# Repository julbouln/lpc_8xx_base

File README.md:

[NXP's LPC800 family microcontroller](http://www.nxp.com/products/microcontrollers/cortex_m0_m0/lpc800/) development code base.

The code should work with LPC810, LPC811 and LPC812.

The code is based on [LPCOpen 2](http://www.lpcware.com/content/nxpfile/lpcopen-software-development-platform-lpc8xx-packages) source code and [sebseb7/lpc8xx Makefile](https://github.com/sebseb7/lpc8xx) (arm-none-eabi toolchain). The main addition is C++ capability and an Arduino like compatible API.

Supported Arduino functions and libraries :

* pinMode, digitalWrite, digitalRead
* delay
* Serial
* SPI
* Wire

INO files can be compiled with ino2firmware.sh script.

Code come with an hardware implementation composed of a MCP2200 USB to UART and a LPC812 chip.
https://github.com/julbouln/mcp2200_simpleio and lpc21isp must be installed and tools in tools/ compiled to use "make flash" which upload firmware.hex.

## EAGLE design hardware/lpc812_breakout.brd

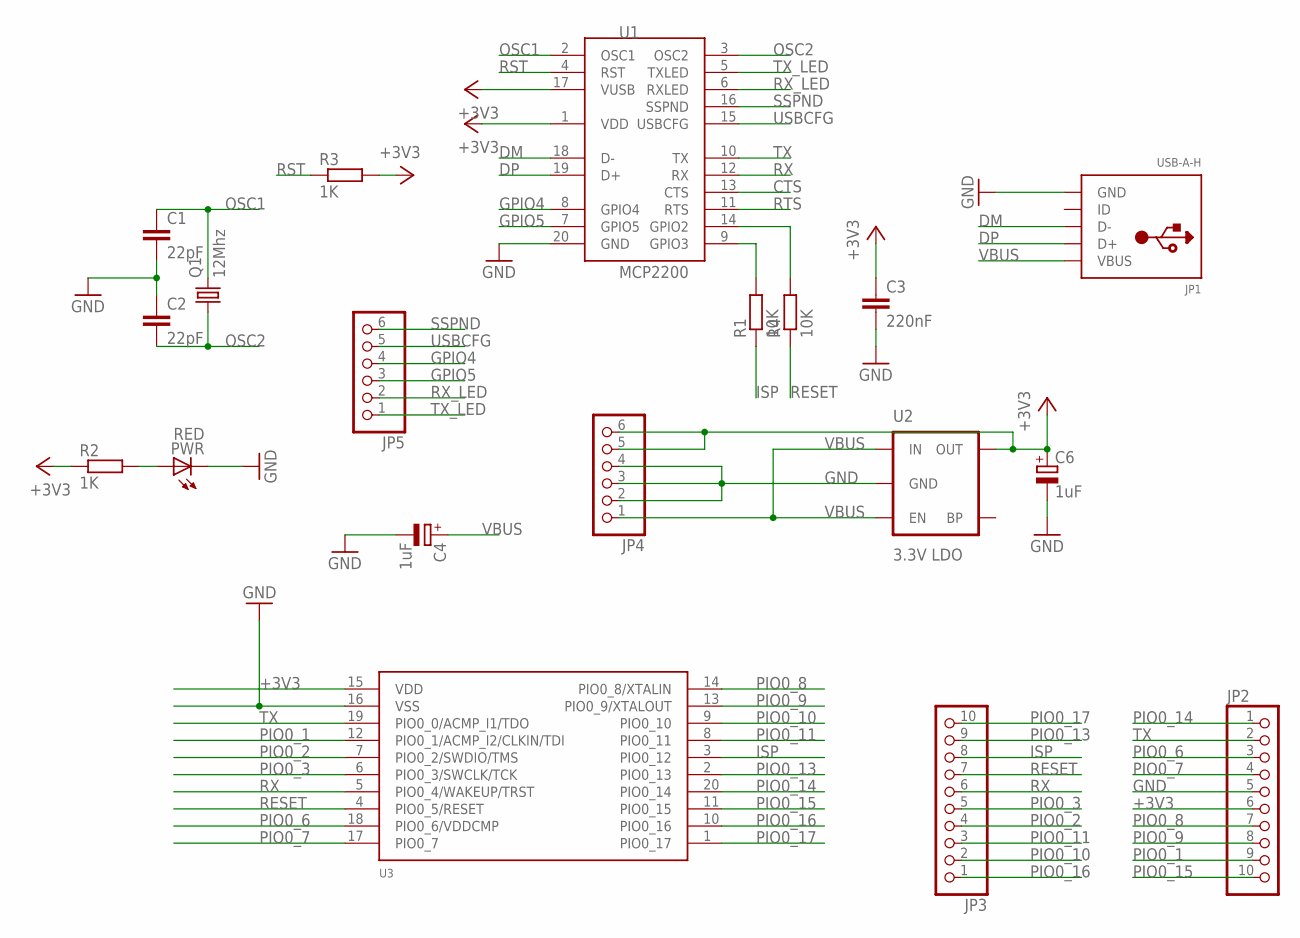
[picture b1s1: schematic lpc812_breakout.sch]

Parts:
C1, C2: 22pF; C1206
C3: 220nF; C1206
C4, C6: 1uF; A/3216-18R
JP1: USB-A-H; USB-MINIB-THM-MOLEX
JP2, JP3: HEADER-1X10ROUND; 1X10_ROUND
JP4, JP5: HEADER-1X6ROUND; 1X06_ROUND
PWR: RED; 1206
Q1: 12Mhz; HC49/S
R1, R4: 10K; R1206
R2, R3: 1K; R1206
U1: MCP2200; SSOP20
U2: 3.3V LDO; SOT23-5
U3: LPC812M101JDH20; TSSOP20

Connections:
+3V3: C3.1, C6.+, JP2.6, JP4.5, JP4.6, R2.1, R3.2, U1.1 (VDD), U1.17 (VUSB), U2.5 (OUT), U3.15 (VDD)
CTS: U1.13 (CTS)
DM: JP1.D-, U1.18 (D-)
DP: JP1.D+, U1.19 (D+)
GND: C1.2, C2.1, C3.2, C4.-, C6.-, JP1.GND, JP2.5, JP4.2, JP4.3, JP4.4, PWR.C, U1.20 (GND), U2.2 (GND), U3.16 (VSS)
GPIO4: JP5.4, U1.8 (GPIO4)
GPIO5: JP5.3, U1.7 (GPIO5)
ISP: JP3.8, R1.1, U3.3 (PIO0_12)
unnamed: PWR.A, R2.2
unnamed: R1.2, U1.9 (GPIO3)
unnamed: R4.2, U1.14 (GPIO2)
OSC1: C1.1, Q1.2, U1.2 (OSC1)
OSC2: C2.2, Q1.1, U1.3 (OSC2)
PIO0_1: JP2.9, U3.12 (PIO0_1/ACMP_I2/CLKIN/TDI)
PIO0_2: JP3.4, U3.7 (PIO0_2/SWDIO/TMS)
PIO0_3: JP3.5, U3.6 (PIO0_3/SWCLK/TCK)
PIO0_6: JP2.3, U3.18 (PIO0_6/VDDCMP)
PIO0_7: JP2.4, U3.17 (PIO0_7)
PIO0_8: JP2.7, U3.14 (PIO0_8/XTALIN)
PIO0_9: JP2.8, U3.13 (PIO0_9/XTALOUT)
PIO0_10: JP3.2, U3.9 (PIO0_10)
PIO0_11: JP3.3, U3.8 (PIO0_11)
PIO0_13: JP3.9, U3.2 (PIO0_13)
PIO0_14: JP2.1, U3.20 (PIO0_14)
PIO0_15: JP2.10, U3.11 (PIO0_15)
PIO0_16: JP3.1, U3.10 (PIO0_16)
PIO0_17: JP3.10, U3.1 (PIO0_17)
RESET: JP3.7, R4.1, U3.4 (PIO0_5/RESET)
RST: R3.1, U1.4 (RST)
RTS: U1.11 (RTS)
RX: JP3.6, U1.12 (RX), U3.5 (PIO0_4/WAKEUP/TRST)
RX_LED: JP5.2, U1.6 (RXLED)
SSPND: JP5.6, U1.16 (SSPND)
TX: JP2.2, U1.10 (TX), U3.19 (PIO0_0/ACMP_I1/TDO)
TX_LED: JP5.1, U1.5 (TXLED)
USBCFG: JP5.5, U1.15 (USBCFG)
VBUS: C4.+, JP1.VBUS, JP4.1, U2.1 (IN), U2.3 (EN)

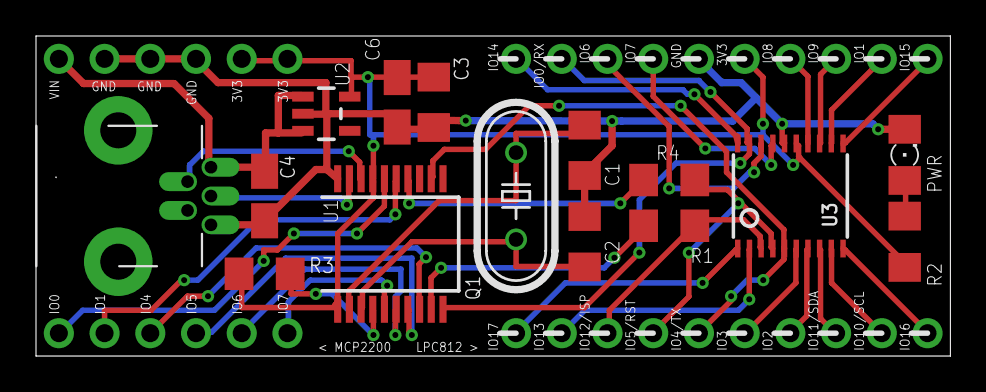
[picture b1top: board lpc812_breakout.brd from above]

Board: 2 copper layers, 50.8 x 17.8 mm, 20 parts (1 on the bottom side), 35 nets.

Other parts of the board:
U$1: PANDA

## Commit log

2014-06-14 cleanup
2014-06-15 improvements
2014-06-16 cpp support
2014-06-16 cpp support lpc810 and lpc811, maybe too much for these chips
2014-08-02 i2c and misc fixes
2014-08-03 fast math and printf
2014-09-28 i2c fix and example + hardware
2014-09-28 tools missing
2014-09-28 better integration with existing ino
2014-11-02 cleanup + map + Servo
2014-11-02 avoid conflict with arduino like code

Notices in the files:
parts and their libraries:
microbuilder: This work is placed in the public domain, and may be freely used for commercial and non-commercial work with the following conditions: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
